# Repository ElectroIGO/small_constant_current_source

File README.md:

# small_constant_current_source
Provides constants current to particular load. This configuration provides 10 mA current to temperature sensor.

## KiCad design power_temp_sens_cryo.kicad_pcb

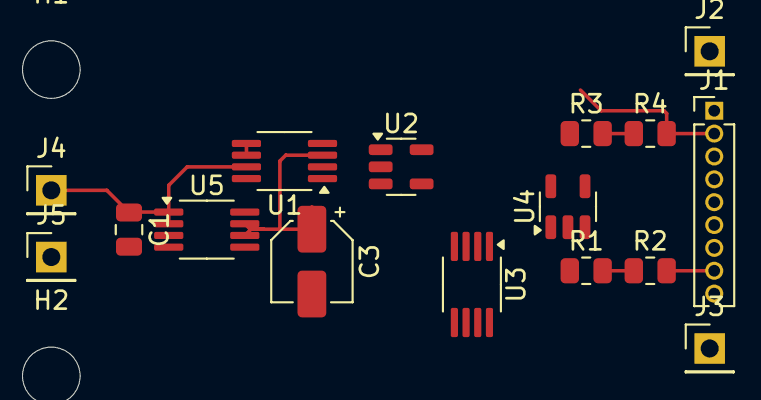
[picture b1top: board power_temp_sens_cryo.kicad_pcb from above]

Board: 2 copper layers, 20 parts (0 on the bottom side), 13 nets.

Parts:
C1: 0.1 uF; C_0805_2012Metric
C3: 10 uF; CP_Elec_4x5.4
H1, H2, H3, H4: MountingHole; MountingHole_3.2mm_M3
J1: temp. sens.; PinHeader_1x09_P1.27mm_Vertical
J2: MCU_ADC1; PinHeader_1x01_P2.54mm_Vertical
J3: MCU_ADC0; PinHeader_1x01_P2.54mm_Vertical
J4: 5V; PinHeader_1x01_P2.54mm_Vertical
J5: GND; PinHeader_1x01_P2.54mm_Vertical
R1, R3: 100k; R_0805_2012Metric
R2, R4: 25.2k; R_0805_2012Metric
U1, U3: AD8276; MSOP-8_3x3mm_P0.65mm
U2, U4: AD8603; TSOT-23-5
U5: MSOP-8_3x3mm_P0.65mm

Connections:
+5V: C1.1, J4.1, U1.7 (V+), U2.5 (V+), U3.7 (V+), U4.5 (V+), U5.1 (~SHDN), U5.2 (Vin)
/IA+: J1.2, R4.2, U2.3 (+)
/IB+: J1.8, R2.2, U4.3 (+)
/VA+: J1.3, J2.1
/VB+: J1.6, J3.1
/Vref+: C3.1, U1.3 (+), U3.3 (+), U5.6 (VoutS), U5.7 (VoutF)
GND: C1.2, C3.2, J1.4, J1.5, J1.7, J1.9, J5.1, U1.2 (-), U1.4 (V-), U2.2 (V-), U3.2 (-), U3.4 (V-), U4.2 (V-), U5.3 (GND), U5.4 (GND), U5.5 (GND), U5.8 (GND)
unnamed: R1.2, R2.1
unnamed: R3.2, R4.1
unnamed: U1.1 (REF), U2.1, U2.4 (-)
unnamed: R3.1, U1.5 (SENSE), U1.6
unnamed: U3.1 (REF), U4.1, U4.4 (-)
unnamed: R1.1, U3.5 (SENSE), U3.6

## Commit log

2025-03-13 Schematics finished. Needs to add all footprints and design the pcb for production.
2025-03-17 unfinished project
